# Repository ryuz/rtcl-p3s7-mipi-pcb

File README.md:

English version: [README_en.md](README_en.md)

# グローバルシャッターMIPI高速度カメラ(PYTHON300 + Spartan7)

## 概要

[こちら](https://rtc-lab.com/products/rtcl-cam-p3s7-mipi/)で紹介しておりますグローバルシャッターMIPI高速度カメラの KiCAD による設計データです。

オンセミコンダクター社 [PYTHON300イメージセンサー](https://www.onsemi.jp/products/sensors/image-sensors/python300) と AMD(Xilinx) の [Spartan7](https://www.amd.com/ja/products/adaptive-socs-and-fpgas/fpga/spartan-7.html) FPGA を用いた研究開発向けの小型のカメラモジュールです。

データシート上は VGA サイズながら 815fps の高速度撮影が可能と記載されているセンサーを利用しており、当方では [KV260](https://www.amd.com/ja/products/system-on-modules/kria/k26/kv260-vision-starter-kit.html) と [Zybo Z7](https://digilent.com/shop/zybo-z7-zynq-7000-arm-fpga-soc-development-board/) に接続して 320x320 サイズで 1000fps 撮像が出来ております。

撮影動画なども[こちら](https://rtc-lab.com/products/rtcl-cam-p3s7-mipi/)で紹介しております。

## 回路図

回路図は以下です。

- [イメージセンサー子基板](sensor_python300/sensor_python300.pdf)
- [FPGA親基板](mipi_spartan7/mipi_spartan7.pdf)

## 基板販売

当方で製造したものを[BOOTH](https://rtc-lab.booth.pm/)にて販売中です。

- [モノクロ版](https://rtc-lab.booth.pm/items/7427869)
- [カラー版](https://rtc-lab.booth.pm/items/7428802)

## 関連ソフトウェア

現時点では、KV260 に独自仕様でデータを送るプロジェクトがあります。

- [Spartan-7 のデザイン](https://github.com/ryuz/rtcl-designs/tree/main/projects/rtcl_p3s7_mipi/rtcl_p3s7_mipi)
- [KV260 の デザイン](https://github.com/ryuz/rtcl-designs/tree/main/projects/kv260/kv260_rtcl_p3s7_hs)

他に速度を落として ZYBO と接続できる事や、MIPI-CSI に準拠することも可能なことを確認していますが、まだプロジェクトとして準備できておりませんので今後にご期待ください。

## リポジトリ構成

| ディレクトリ |  説明                                            |
|:------------|:------------------------------------------------|
| mipi_spartan7    | Spartan7 FPGA の載った親基板のプロジェクト |
| sensor_python300 | PYTHON300 イメージセンサーの載った子基板のプロジェクト |
| sensor_mipi      | 親子基板を共取り製造用に結合したプロジェクト |

## 免責事項

本設計データは、研究開発用の試作実験に用するものであり、利用に際して発生した如何なる損害も作者は補償いたしませんので予めご了承ください。

## ライセンス(License)

本設計データは、[クリエイティブ・コモンズ 表示-非営利 4.0 国際 ライセンス](https://creativecommons.org/licenses/by-nc/4.0/deed.ja)の下で提供されています。

製造した本基板の無断での販売や配布を行わない限りは、趣味や研究開発用途でご自由にお使いいただく事が出来ます。

また、商用に製造販売を希望される場合は、別途ライセンス契約を作者までご相談ください。[お問い合わせフォーム](https://rtc-lab.com/contact/)などからお問い合わせ頂けます。

## 作者情報

渕上 竜司(Ryuji Fuchikami)
[リアルタイムコンピューティング研究所](https://rtc-lab.com/)

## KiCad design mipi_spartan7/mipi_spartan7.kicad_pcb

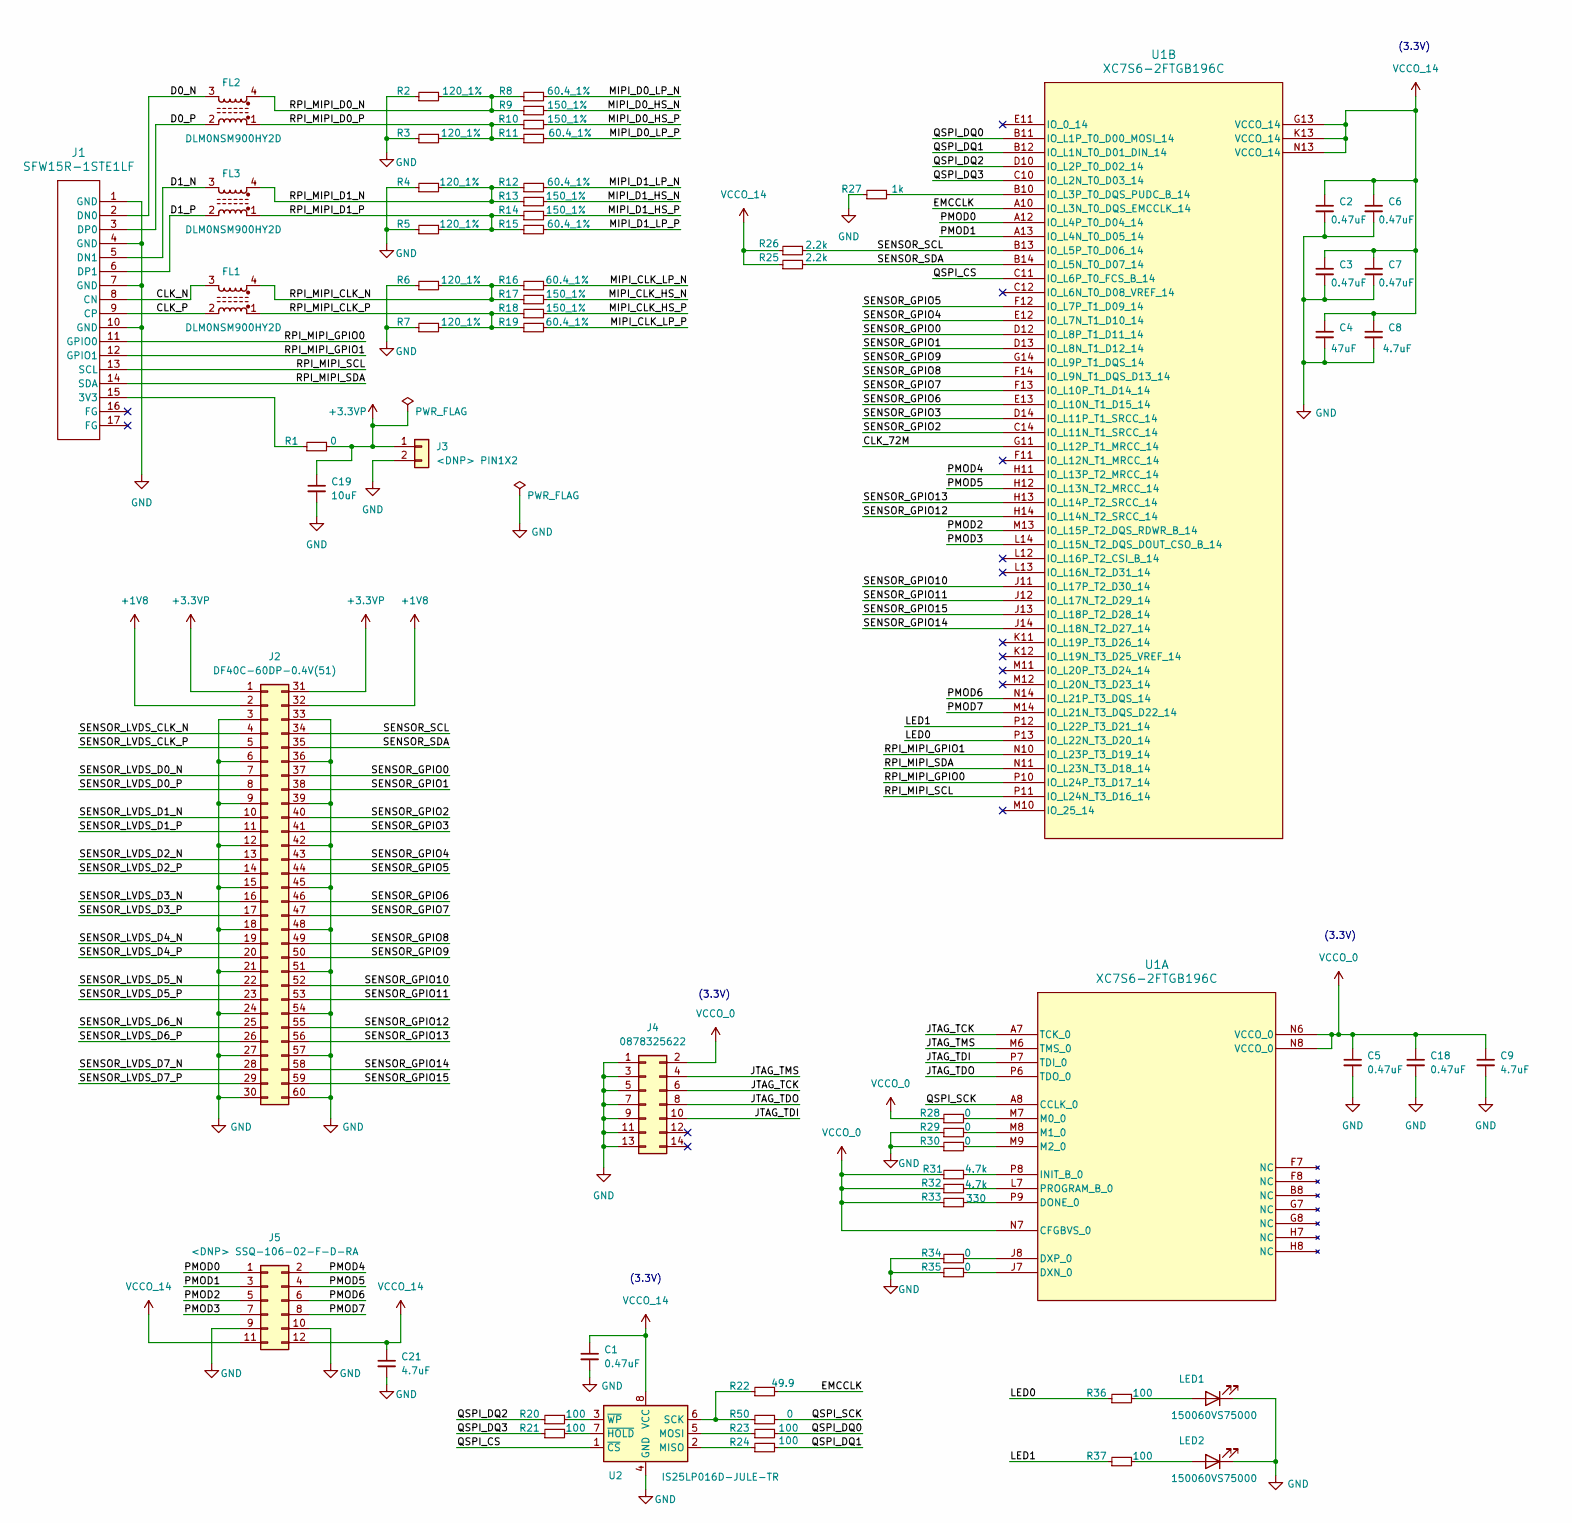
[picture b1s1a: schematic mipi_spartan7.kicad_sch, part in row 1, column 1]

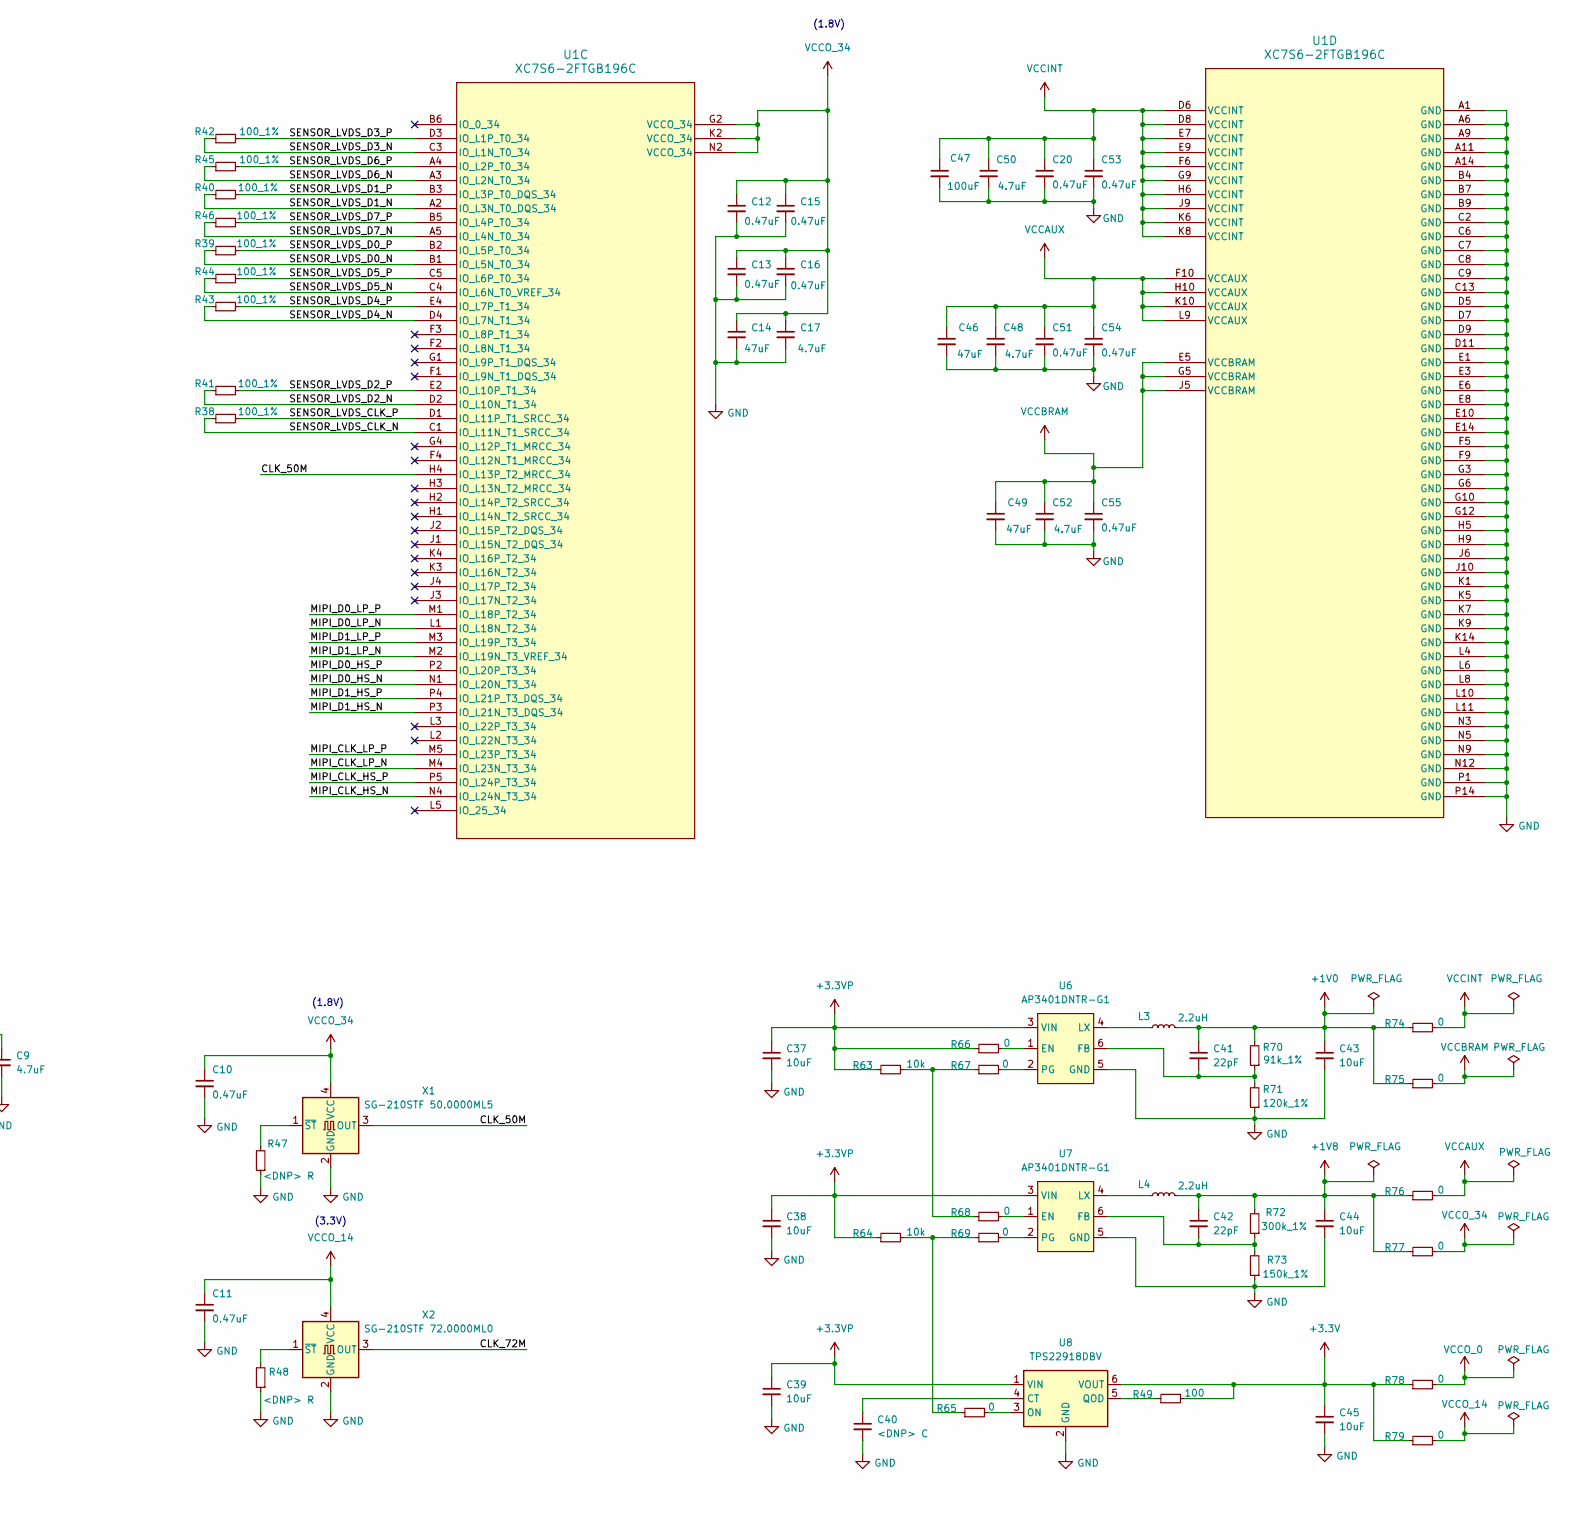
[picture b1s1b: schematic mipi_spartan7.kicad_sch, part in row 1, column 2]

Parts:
C1, C2, C3, C5, C6, C7, C10, C11, C12, C13, C15, C16, C18, C20, C51, C53, C54, C55: 0.47uF; C_0402_1005Metric
C4, C14, C46, C49: 47uF; C_0603_1608Metric
C8, C9, C17, C21, C48, C50, C52: 4.7uF; C_0402_1005Metric
C19, C37, C38, C39, C43, C44, C45: 10uF; C_0603_1608Metric
C40: <DNP> C; L_0402_1005Metric
C41, C42: 22pF; L_0402_1005Metric
C47: 100uF; C_1206_3216Metric
FL1, FL2, FL3: DLM0NSM900HY2D; JLC C1857796
J1: SFW15R-1STE1LF
J2: DF40C-60DP-0.4V(51); DF40C-60DP-0.4V51
J3: <DNP> PIN1X2; PH_01x02_2.54mm_NoSilk
J4: 0878325622; 878325622
J5: <DNP> SSQ-106-02-F-D-RA; PH_02x06_2.54mm
L3, L4: 2.2uH; L_1008_2520Metric
LED1, LED2: 150060VS75000; LED_0603_1608Metric
R1, R28, R29, R30, R34, R35, R50, R65, R66, R67, R68, R69, R74, R75, R76, R77, R78, R79: 0; R_0402_1005Metric
R2, R3, R4, R5, R6, R7: 120_1%; R_0402_1005Metric
R8, R11, R12, R15, R16, R19: 60.4_1%; R_0402_1005Metric
R9, R10, R13, R14, R17, R18: 150_1%; R_0402_1005Metric
R20, R21, R23, R24, R36, R37, R49: 100; R_0402_1005Metric
R22: 49.9; R_0402_1005Metric
R25, R26: 2.2k; R_0402_1005Metric
R27: 1k; R_0402_1005Metric
R31, R32: 4.7k; R_0402_1005Metric
R33: 330; R_0402_1005Metric
R38, R39, R40, R41, R42, R43, R44, R45, R46: 100_1%; R_0402_1005Metric
R47, R48: <DNP> R; R_0402_1005Metric
R63, R64: 10k; R_0402_1005Metric
R70: 91k_1%; R_0402_1005Metric
R71: 120k_1%; R_0402_1005Metric
R72: 300k_1%; R_0402_1005Metric
R73: 150k_1%; R_0402_1005Metric
U1: XC7S6-2FTGB196C; FTGB196
U2: IS25LP016D-JULE-TR
U6, U7: AP3401DNTR-G1; Diodes_UDFN2020-6_Type-J
U8: TPS22918DBV; SOT-23-6
X1: SG-210STF 50.0000ML5; SG-210STF
X2: SG-210STF 72.0000ML0; SG-210STF

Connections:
+1V0: C41.1, C43.1, L3.2, R70.2, R74.1, R75.1
+1V8: C42.1, C44.1, J2.2, J2.32, L4.2, R72.2, R76.1, R77.1
+3.3V: C45.1, R49.2, R78.1, R79.1, U8.6 (VOUT)
+3.3VP: C19.1, C37.1, C38.1, C39.1, J2.1, J2.31, J3.1, R1.2, R63.1, R64.1, R66.1, U6.3 (VIN), U7.3 (VIN), U8.1 (VIN)
/CLK_50M: U1.H4 (IO_L13P_T2_MRCC_34), X1.3 (OUT)
/CLK_72M: U1.G11 (IO_L12P_T1_MRCC_14), X2.3 (OUT)
/CLK_N: FL1.3, J1.8 (CN)
/CLK_P: FL1.2, J1.9 (CP)
/D0_N: FL2.3, J1.2 (DN0)
/D0_P: FL2.2, J1.3 (DP0)
/D1_N: FL3.3, J1.5 (DN1)
/D1_P: FL3.2, J1.6 (DP1)
/EMCCLK: R22.2, U1.A10 (IO_L3N_T0_DQS_EMCCLK_14)
/JTAG_TCK: J4.6, U1.A7 (TCK_0)
/JTAG_TDI: J4.10, U1.P7 (TDI_0)
/JTAG_TDO: J4.8, U1.P6 (TDO_0)
/JTAG_TMS: J4.4, U1.M6 (TMS_0)
/LED0: R36.1, U1.P13 (IO_L22N_T3_D20_14)
/LED1: R37.1, U1.P12 (IO_L22P_T3_D21_14)
/MIPI_CLK_HS_N: R17.2, U1.N4 (IO_L24N_T3_34)
/MIPI_CLK_HS_P: R18.2, U1.P5 (IO_L24P_T3_34)
/MIPI_CLK_LP_N: R16.2, U1.M4 (IO_L23N_T3_34)
/MIPI_CLK_LP_P: R19.2, U1.M5 (IO_L23P_T3_34)
/MIPI_D0_HS_N: R9.2, U1.N1 (IO_L20N_T3_34)
/MIPI_D0_HS_P: R10.2, U1.P2 (IO_L20P_T3_34)
/MIPI_D0_LP_N: R8.2, U1.L1 (IO_L18N_T2_34)
/MIPI_D0_LP_P: R11.2, U1.M1 (IO_L18P_T2_34)
/MIPI_D1_HS_N: R13.2, U1.P3 (IO_L21N_T3_DQS_34)
/MIPI_D1_HS_P: R14.2, U1.P4 (IO_L21P_T3_DQS_34)
/MIPI_D1_LP_N: R12.2, U1.M2 (IO_L19N_T3_VREF_34)
/MIPI_D1_LP_P: R15.2, U1.M3 (IO_L19P_T3_34)
/PMOD0: J5.1, U1.A12 (IO_L4P_T0_D04_14)
/PMOD1: J5.3, U1.A13 (IO_L4N_T0_D05_14)
/PMOD2: J5.5, U1.M13 (IO_L15P_T2_DQS_RDWR_B_14)
/PMOD3: J5.7, U1.L14 (IO_L15N_T2_DQS_DOUT_CSO_B_14)
/PMOD4: J5.2, U1.H11 (IO_L13P_T2_MRCC_14)
/PMOD5: J5.4, U1.H12 (IO_L13N_T2_MRCC_14)
/PMOD6: J5.6, U1.N14 (IO_L21P_T3_DQS_14)
/PMOD7: J5.8, U1.M14 (IO_L21N_T3_DQS_D22_14)
/QSPI_CS: U1.C11 (IO_L6P_T0_FCS_B_14), U2.1 (~CS)
/QSPI_DQ0: R23.2, U1.B11 (IO_L1P_T0_D00_MOSI_14)
/QSPI_DQ1: R24.2, U1.B12 (IO_L1N_T0_D01_DIN_14)
/QSPI_DQ2: R20.1, U1.D10 (IO_L2P_T0_D02_14)
/QSPI_DQ3: R21.1, U1.C10 (IO_L2N_T0_D03_14)
/QSPI_SCK: R50.2, U1.A8 (CCLK_0)
/RPI_MIPI_CLK_N: FL1.4, R6.2, R16.1, R17.1
/RPI_MIPI_CLK_P: FL1.1, R7.2, R18.1, R19.1
/RPI_MIPI_D0_N: FL2.4, R2.2, R8.1, R9.1
/RPI_MIPI_D0_P: FL2.1, R3.2, R10.1, R11.1
/RPI_MIPI_D1_N: FL3.4, R4.2, R12.1, R13.1
/RPI_MIPI_D1_P: FL3.1, R5.2, R14.1, R15.1
/RPI_MIPI_GPIO0: J1.11 (GPIO0), U1.P10 (IO_L24P_T3_D17_14)
/RPI_MIPI_GPIO1: J1.12 (GPIO1), U1.N10 (IO_L23P_T3_D19_14)
/RPI_MIPI_SCL: J1.13 (SCL), U1.P11 (IO_L24N_T3_D16_14)
/RPI_MIPI_SDA: J1.14 (SDA), U1.N11 (IO_L23N_T3_D18_14)
/SENSOR_GPIO0: J2.37, U1.D12 (IO_L8P_T1_D11_14)
/SENSOR_GPIO1: J2.38, U1.D13 (IO_L8N_T1_D12_14)
/SENSOR_GPIO2: J2.40, U1.C14 (IO_L11N_T1_SRCC_14)
/SENSOR_GPIO3: J2.41, U1.D14 (IO_L11P_T1_SRCC_14)
/SENSOR_GPIO4: J2.43, U1.E12 (IO_L7N_T1_D10_14)
/SENSOR_GPIO5: J2.44, U1.F12 (IO_L7P_T1_D09_14)
/SENSOR_GPIO6: J2.46, U1.E13 (IO_L10N_T1_D15_14)
/SENSOR_GPIO7: J2.47, U1.F13 (IO_L10P_T1_D14_14)
/SENSOR_GPIO8: J2.49, U1.F14 (IO_L9N_T1_DQS_D13_14)
/SENSOR_GPIO9: J2.50, U1.G14 (IO_L9P_T1_DQS_14)
/SENSOR_GPIO10: J2.52, U1.J11 (IO_L17P_T2_D30_14)
/SENSOR_GPIO11: J2.53, U1.J12 (IO_L17N_T2_D29_14)
/SENSOR_GPIO12: J2.55, U1.H14 (IO_L14N_T2_SRCC_14)
/SENSOR_GPIO13: J2.56, U1.H13 (IO_L14P_T2_SRCC_14)
/SENSOR_GPIO14: J2.58, U1.J14 (IO_L18N_T2_D27_14)
/SENSOR_GPIO15: J2.59, U1.J13 (IO_L18P_T2_D28_14)
/SENSOR_LVDS_CLK_N: J2.4, R38.1, U1.C1 (IO_L11N_T1_SRCC_34)
/SENSOR_LVDS_CLK_P: J2.5, R38.2, U1.D1 (IO_L11P_T1_SRCC_34)
/SENSOR_LVDS_D0_N: J2.7, R39.1, U1.B1 (IO_L5N_T0_34)
/SENSOR_LVDS_D0_P: J2.8, R39.2, U1.B2 (IO_L5P_T0_34)
/SENSOR_LVDS_D1_N: J2.10, R40.1, U1.A2 (IO_L3N_T0_DQS_34)
/SENSOR_LVDS_D1_P: J2.11, R40.2, U1.B3 (IO_L3P_T0_DQS_34)
/SENSOR_LVDS_D2_N: J2.13, R41.1, U1.D2 (IO_L10N_T1_34)
/SENSOR_LVDS_D2_P: J2.14, R41.2, U1.E2 (IO_L10P_T1_34)
/SENSOR_LVDS_D3_N: J2.16, R42.1, U1.C3 (IO_L1N_T0_34)
/SENSOR_LVDS_D3_P: J2.17, R42.2, U1.D3 (IO_L1P_T0_34)
/SENSOR_LVDS_D4_N: J2.19, R43.1, U1.D4 (IO_L7N_T1_34)
/SENSOR_LVDS_D4_P: J2.20, R43.2, U1.E4 (IO_L7P_T1_34)
/SENSOR_LVDS_D5_N: J2.22, R44.1, U1.C4 (IO_L6N_T0_VREF_34)
/SENSOR_LVDS_D5_P: J2.23, R44.2, U1.C5 (IO_L6P_T0_34)
/SENSOR_LVDS_D6_N: J2.25, R45.1, U1.A3 (IO_L2N_T0_34)
/SENSOR_LVDS_D6_P: J2.26, R45.2, U1.A4 (IO_L2P_T0_34)
/SENSOR_LVDS_D7_N: J2.28, R46.1, U1.A5 (IO_L4N_T0_34)
/SENSOR_LVDS_D7_P: J2.29, R46.2, U1.B5 (IO_L4P_T0_34)
/SENSOR_SCL: J2.34, R26.2, U1.B13 (IO_L5P_T0_D06_14)
/SENSOR_SDA: J2.35, R25.2, U1.B14 (IO_L5N_T0_D07_14)
GND: C1.2, C2.2, C3.2, C4.2, C5.2, C6.2, C7.2, C8.2, C9.2, C10.2, C11.2, C12.2, C13.2, C14.2, C15.2, C16.2, C17.2, C18.2, C19.2, C20.2, C21.2, C37.2, C38.2, C39.2, C40.2, C43.2, C44.2, C45.2, C46.2, C47.2, C48.2, C49.2, C50.2, C51.2, C52.2, C53.2, C54.2, C55.2, J1.1 (GND), J1.4 (GND), J1.7 (GND), J1.10 (GND), J2.3, J2.6, J2.9, J2.12, J2.15, J2.18, J2.21, J2.24, J2.27, J2.30, J2.33, J2.36, J2.39, J2.42, J2.45, J2.48, J2.51, J2.54, J2.57, J2.60, J3.2, J4.1, J4.3, J4.5, J4.7, J4.9, J4.11, J4.13, J5.9, J5.10, LED1.1 (K), LED2.1 (K), R2.1, R3.1, R4.1, R5.1, R6.1, R7.1, R27.1, R29.1, R30.1, R34.1, R35.1, R47.1, R48.1, R71.1, R73.1, U1.A1 (GND), U1.A6 (GND), U1.A9 (GND), U1.A11 (GND), U1.A14 (GND), U1.B4 (GND), U1.B7 (GND), U1.B9 (GND), U1.C2 (GND), U1.C6 (GND), U1.C7 (GND), U1.C8 (GND), U1.C9 (GND), U1.C13 (GND), U1.D5 (GND), U1.D7 (GND), U1.D9 (GND), U1.D11 (GND), U1.E1 (GND), U1.E3 (GND), U1.E6 (GND), U1.E8 (GND), U1.E10 (GND), U1.E14 (GND), U1.F5 (GND), U1.F9 (GND), U1.G3 (GND), U1.G6 (GND), U1.G10 (GND), U1.G12 (GND), U1.H5 (GND), U1.H9 (GND), U1.J6 (GND), U1.J10 (GND), U1.K1 (GND), U1.K5 (GND), U1.K7 (GND), U1.K9 (GND), U1.K14 (GND), U1.L4 (GND), U1.L6 (GND), U1.L8 (GND), U1.L10 (GND), U1.L11 (GND), U1.N3 (GND), U1.N5 (GND), U1.N9 (GND), U1.N12 (GND), U1.P1 (GND), U1.P14 (GND), U2.4 (GND), U6.5 (GND), U7.5 (GND), U8.2 (GND), X1.2 (GND), X2.2 (GND)
unnamed: J1.15 (3V3), R1.1
unnamed: LED1.2 (A), R36.2
unnamed: LED2.2 (A), R37.2
unnamed: R63.2, R67.1, R68.1
unnamed: R64.2, R65.1, R69.1
unnamed: R33.2, U1.P9 (DONE_0)
unnamed: R35.2, U1.J7 (DXN_0)
unnamed: R34.2, U1.J8 (DXP_0)
unnamed: R31.2, U1.P8 (INIT_B_0)
unnamed: R28.2, U1.M7 (M0_0)
unnamed: R29.2, U1.M8 (M1_0)
unnamed: R30.2, U1.M9 (M2_0)
unnamed: R32.2, U1.L7 (PROGRAM_B_0)
unnamed: R27.2, U1.B10 (IO_L3P_T0_DQS_PUDC_B_14)
unnamed: R24.1, U2.2 (MISO)
unnamed: R23.1, U2.5 (MOSI)
unnamed: R22.1, R50.1, U2.6 (SCK)
unnamed: R21.2, U2.7 (~HOLD)
unnamed: R20.2, U2.3 (~WP)
unnamed: R66.2, U6.1 (EN)
unnamed: C41.2, R70.1, R71.2, U6.6 (FB)
unnamed: L3.1, U6.4 (LX)
unnamed: R67.2, U6.2 (PG)
unnamed: R68.2, U7.1 (EN)
unnamed: C42.2, R72.1, R73.2, U7.6 (FB)
unnamed: L4.1, U7.4 (LX)
unnamed: R69.2, U7.2 (PG)
unnamed: C40.1, U8.4 (CT)
unnamed: R65.2, U8.3 (ON)
unnamed: R49.1, U8.5 (QOD)
unnamed: R47.2, X1.1 (~ST)
unnamed: R48.2, X2.1 (~ST)
VCCAUX: C46.1, C48.1, C51.1, C54.1, R76.2, U1.F10 (VCCAUX), U1.H10 (VCCAUX), U1.K10 (VCCAUX), U1.L9 (VCCAUX)
VCCBRAM: C49.1, C52.1, C55.1, R75.2, U1.E5 (VCCBRAM), U1.G5 (VCCBRAM), U1.J5 (VCCBRAM)
VCCINT: C20.1, C47.1, C50.1, C53.1, R74.2, U1.D6 (VCCINT), U1.D8 (VCCINT), U1.E7 (VCCINT), U1.E9 (VCCINT), U1.F6 (VCCINT), U1.G9 (VCCINT), U1.H6 (VCCINT), U1.J9 (VCCINT), U1.K6 (VCCINT), U1.K8 (VCCINT)
VCCO_0: C5.1, C9.1, C18.1, J4.2, R28.1, R31.1, R32.1, R33.1, R78.2, U1.N6 (VCCO_0), U1.N7 (CFGBVS_0), U1.N8 (VCCO_0)
VCCO_14: C1.1, C2.1, C3.1, C4.1, C6.1, C7.1, C8.1, C11.1, C21.1, J5.11, J5.12, R25.1, R26.1, R79.2, U1.G13 (VCCO_14), U1.K13 (VCCO_14), U1.N13 (VCCO_14), U2.8 (VCC), X2.4 (VCC)
VCCO_34: C10.1, C12.1, C13.1, C14.1, C15.1, C16.1, C17.1, R77.2, U1.G2 (VCCO_34), U1.K2 (VCCO_34), U1.N2 (VCCO_34), X1.4 (VCC)

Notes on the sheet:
(1.8V)
(3.3V)

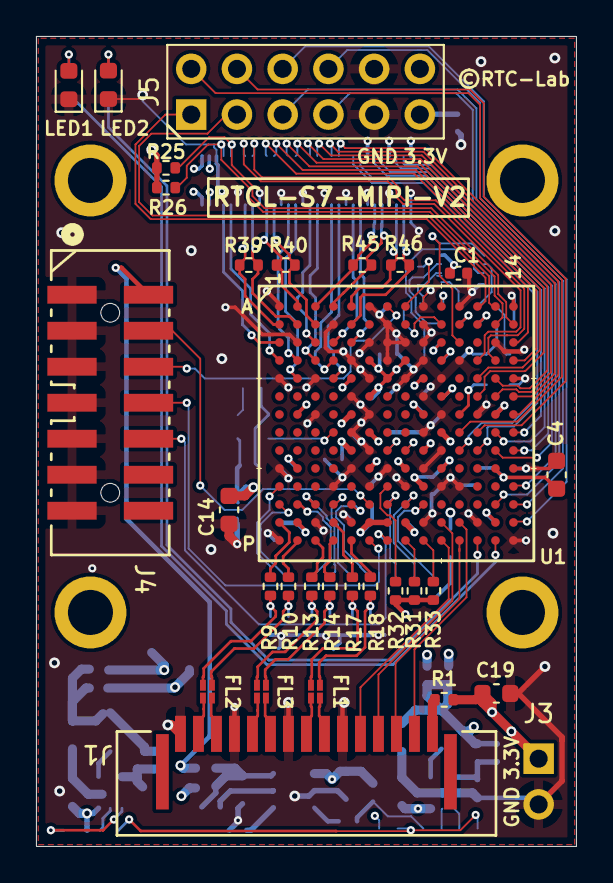
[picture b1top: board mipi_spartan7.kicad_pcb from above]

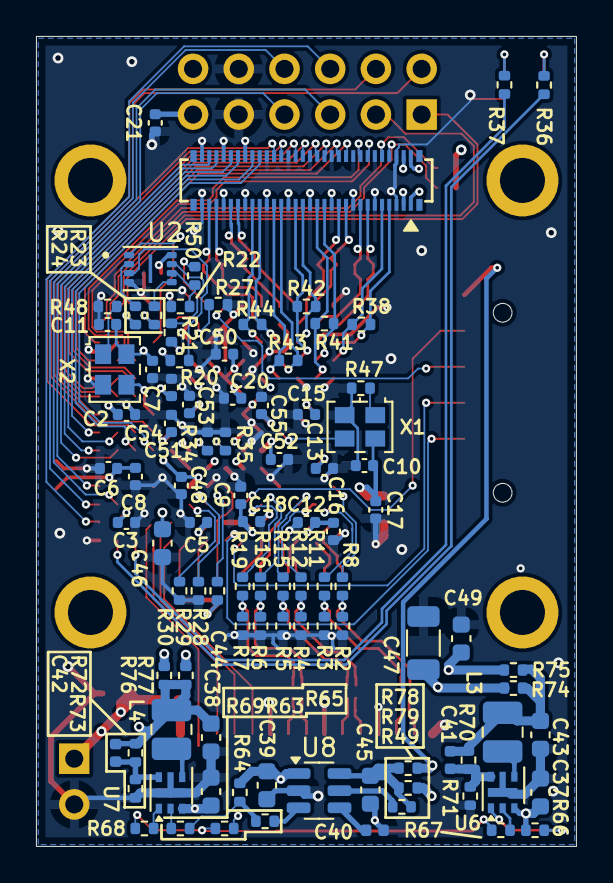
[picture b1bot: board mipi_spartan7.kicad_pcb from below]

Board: 4 copper layers, 30.0 x 45.0 mm, 126 parts (96 on the bottom side), 130 nets.

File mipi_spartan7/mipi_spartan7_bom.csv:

"Reference","Value","Datasheet","Footprint","Qty","DNP"
"C1,C2,C3,C5,C6,C7,C10,C11,C12,C13,C15,C16,C18,C20,C51,C53,C54,C55","0.47uF","~","Capacitor_SMD:C_0402_1005Metric","18",""
"C4,C14,C46,C49","47uF","~","Capacitor_SMD:C_0603_1608Metric","4",""
"C8,C9,C17,C21,C48,C50,C52","4.7uF","~","Capacitor_SMD:C_0402_1005Metric","7",""
"C19,C37,C38,C39,C43,C44,C45","10uF","~","Capacitor_SMD:C_0603_1608Metric","7",""
"C40","<DNP> C","~","Inductor_SMD:L_0402_1005Metric","1",""
"C41,C42","22pF","~","Inductor_SMD:L_0402_1005Metric","2",""
"C47","100uF","~","Capacitor_SMD:C_1206_3216Metric","1",""
"FL1,FL2,FL3","DLM0NSM900HY2D","~","mipi_spartan7:DLM0NSM900HY2D","3",""
"J1","SFW15R-1STE1LF","SFW15R-1STE1LF","mipi_spartan7:SFW15R-1STE1LF","1",""
"J2","DF40C-60DP-0.4V(51)","~","mipi_spartan7:DF40C-60DP-0.4V51","1",""
"J3","<DNP> PIN1X2","~","mipi_spartan7:PH_01x02_2.54mm_NoSilk","1",""
"J4","0878325622","~","mipi_spartan7:878325622","1",""
"J5","<DNP> SSQ-106-02-F-D-RA","~","mipi_spartan7:PH_02x06_2.54mm","1",""
"L3,L4","2.2uH","~","Inductor_SMD:L_1008_2520Metric","2",""
"LED1,LED2","150060VS75000","~","LED_SMD:LED_0603_1608Metric","2",""
"R1,R28,R29,R30,R34,R35,R50,R65,R66,R67,R68,R69,R74,R75,R76,R77,R78,R79","0","~","Resistor_SMD:R_0402_1005Metric","18",""
"R2,R3,R4,R5,R6,R7","120_1%","~","Resistor_SMD:R_0402_1005Metric","6",""
"R8,R11,R12,R15,R16,R19","60.4_1%","~","Resistor_SMD:R_0402_1005Metric","6",""
"R9,R10,R13,R14,R17,R18","150_1%","~","Resistor_SMD:R_0402_1005Metric","6",""
"R20,R21,R23,R24,R36,R37,R49","100","~","Resistor_SMD:R_0402_1005Metric","7",""
"R22","49.9","~","Resistor_SMD:R_0402_1005Metric","1",""
"R25,R26","2.2k","~","Resistor_SMD:R_0402_1005Metric","2",""
"R27","1k","~","Resistor_SMD:R_0402_1005Metric","1",""
"R31,R32","4.7k","~","Resistor_SMD:R_0402_1005Metric","2",""
"R33","330","~","Resistor_SMD:R_0402_1005Metric","1",""
"R38,R39,R40,R41,R42,R43,R44,R45,R46","100_1%","~","Resistor_SMD:R_0402_1005Metric","9",""
"R47,R48","<DNP> R","~","Resistor_SMD:R_0402_1005Metric","2",""
"R63,R64","10k","~","Resistor_SMD:R_0402_1005Metric","2",""
"R70","91k_1%","~","Resistor_SMD:R_0402_1005Metric","1",""
"R71","120k_1%","~","Resistor_SMD:R_0402_1005Metric","1",""
"R72","300k_1%","~","Resistor_SMD:R_0402_1005Metric","1",""
"R73","150k_1%","~","Resistor_SMD:R_0402_1005Metric","1",""
"U1","XC7S6-2FTGB196C","XC7S6-1FTGB196C","mipi_spartan7:FTGB196","1",""
"U2","IS25LP016D-JULE-TR","http://ww1.microchip.com/downloads/en/DeviceDoc/Atmel-8707-S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","mipi_spartan7:IS25LP016D-JULE-TR","1",""
"U6,U7","AP3401DNTR-G1","","mipi_spartan7:Diodes_UDFN2020-6_Type-J","2",""
"U8","TPS22918DBV","http://www.ti.com/lit/ds/symlink/tps22917.pdf","Package_TO_SOT_SMD:SOT-23-6","1",""
"X1","SG-210STF 50.0000ML5","https://support.epson.biz/td/api/doc_check.php?dl=brief_SG50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","Oscillator:Oscillator_SMD_SeikoEpson_SG8002LB-4Pin_5.0x3.2mm","1",""
"X2","SG-210STF 72.0000ML0","https://support.epson.biz/td/api/doc_check.php?dl=brief_SG50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","Oscillator:Oscillator_SMD_SeikoEpson_SG8002LB-4Pin_5.0x3.2mm","1",""

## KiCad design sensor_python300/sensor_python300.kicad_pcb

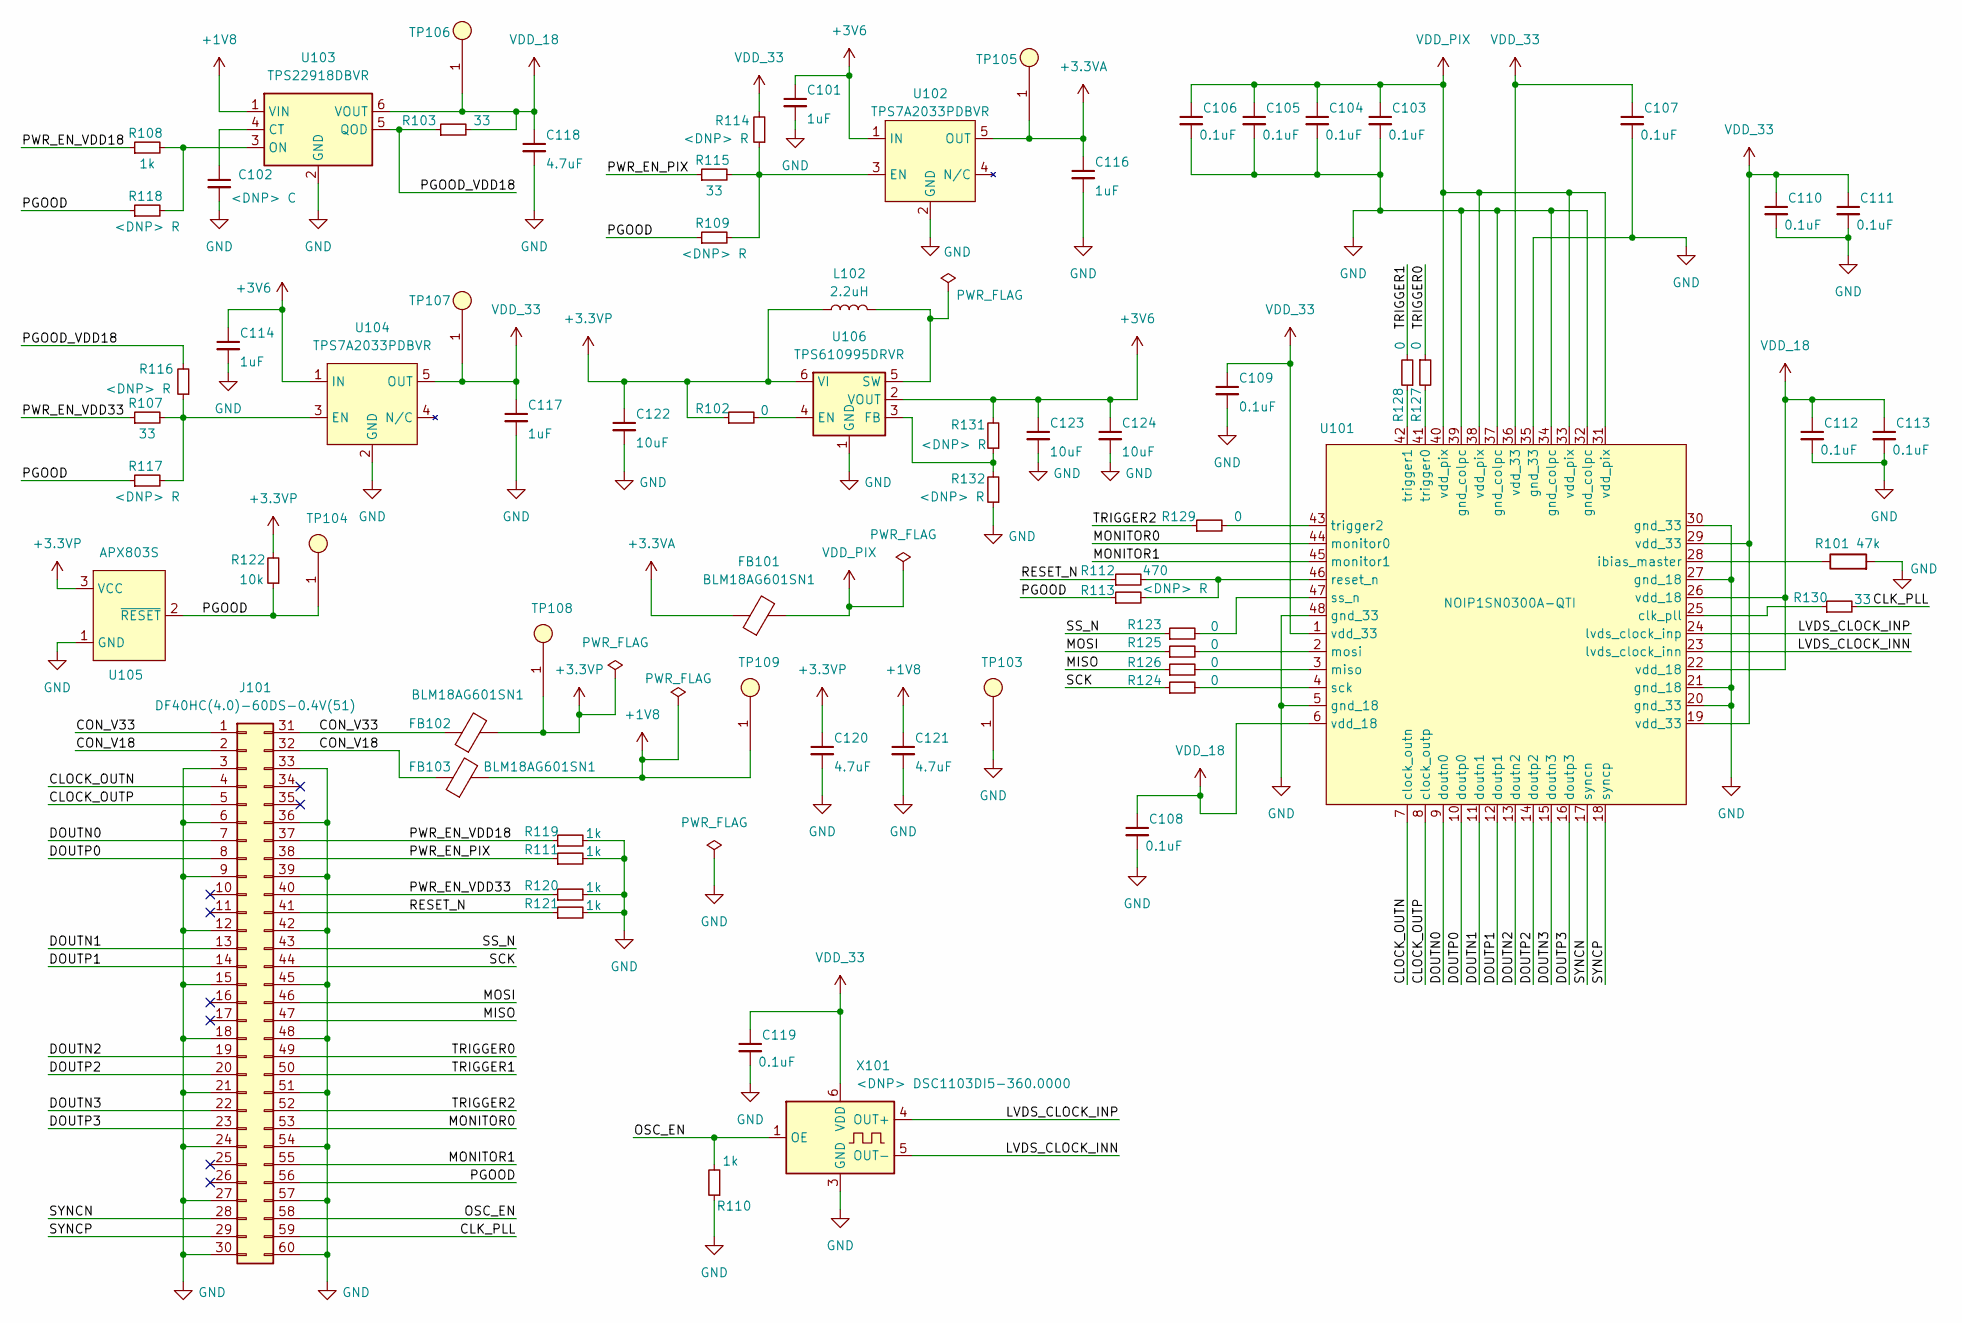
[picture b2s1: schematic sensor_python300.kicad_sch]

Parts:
C101, C114, C116, C117: 1uF; C_0402_1005Metric
C102: <DNP> C; C_0402_1005Metric
C103, C104, C105, C106, C107, C108, C109, C110, C111, C112, C113, C119: 0.1uF; C_0402_1005Metric
C118, C120, C121: 4.7uF; C_0402_1005Metric
C122, C123, C124: 10uF; C_0603_1608Metric
FB101, FB102, FB103: BLM18AG601SN1; L_0603_1608Metric
J101: DF40HC(4.0)-60DS-0.4V(51); DF40HC4.0-60DS-0.4V51
L102: 2.2uH; L_1008_2520Metric
R101: 47k; R_0402_1005Metric
R102, R123, R124, R125, R126, R127, R128, R129: 0; R_0402_1005Metric
R103, R107, R115, R130: 33; R_0402_1005Metric
R108, R110, R111, R119, R120, R121: 1k; R_0402_1005Metric
R109, R113, R114, R116, R117, R118, R131, R132: <DNP> R; R_0402_1005Metric
R112: 470; R_0402_1005Metric
R122: 10k; R_0402_1005Metric
TP103, TP104, TP105, TP106, TP107, TP108, TP109: TestPin
U101: NOIP1SN0300A-QTI; NOIP1SN1300A
U102, U104: TPS7A2033PDBVR; SOT-23-5
U103: TPS22918DBVR; SOT-23-6
U105: APX803S; SOT-23-3
U106: TPS610995DRVR; WSON-6-1EP_2x2mm_P0.65mm_EP1x1.6mm
X101: <DNP> DSC1103DI5-360.0000; Oscillator_SMD_SiTime_PQFD-6L_3.2x2.5mm

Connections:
+1V8: C121.1, FB103.2, TP109.1, U103.1 (VIN)
+3.3VA: C116.1, FB101.1, TP105.1, U102.5 (OUT)
+3.3VP: C120.1, C122.1, FB102.2, L102.1, R102.1, R122.2, TP108.1, U105.3 (VCC), U106.6 (VI)
+3V6: C101.1, C114.1, C123.1, C124.1, R131.2, U102.1 (IN), U104.1 (IN), U106.2 (VOUT)
/CLK_PLL: J101.59, R130.2
/CLOCK_OUTN: J101.4, U101.7 (clock_outn)
/CLOCK_OUTP: J101.5, U101.8 (clock_outp)
/CON_V18: FB103.1, J101.2, J101.32
/CON_V33: FB102.1, J101.1, J101.31
/DOUTN0: J101.7, U101.9 (doutn0)
/DOUTN1: J101.13, U101.11 (doutn1)
/DOUTN2: J101.19, U101.13 (doutn2)
/DOUTN3: J101.22, U101.15 (doutn3)
/DOUTP0: J101.8, U101.10 (doutp0)
/DOUTP1: J101.14, U101.12 (doutp1)
/DOUTP2: J101.20, U101.14 (doutp2)
/DOUTP3: J101.23, U101.16 (doutp3)
/LVDS_CLOCK_INN: U101.23 (lvds_clock_inn), X101.5 (OUT-)
/LVDS_CLOCK_INP: U101.24 (lvds_clock_inp), X101.4 (OUT+)
/MISO: J101.47, R126.1
/MONITOR0: J101.53, U101.44 (monitor0)
/MONITOR1: J101.55, U101.45 (monitor1)
/MOSI: J101.46, R125.1
/OSC_EN: J101.58, R110.2, X101.1 (OE)
/PGOOD: J101.56, R109.1, R113.1, R117.1, R118.1, R122.1, TP104.1, U105.2 (~RESET)
/PGOOD_VDD18: R103.1, R116.2, U103.5 (QOD)
/PWR_EN_PIX: J101.38, R111.1, R115.1
/PWR_EN_VDD18: J101.37, R108.1, R119.1
/PWR_EN_VDD33: J101.40, R107.1, R120.1
/RESET_N: J101.41, R112.1, R121.1
/SCK: J101.44, R124.1
/SS_N: J101.43, R123.1
/SYNCN: J101.28, U101.17 (syncn)
/SYNCP: J101.29, U101.18 (syncp)
/TRIGGER0: J101.49, R127.1
/TRIGGER1: J101.50, R128.2
/TRIGGER2: J101.52, R129.1
GND: C101.2, C102.2, C103.2, C104.2, C105.2, C106.2, C107.2, C108.2, C109.2, C110.2, C111.2, C112.2, C113.2, C114.2, C116.2, C117.2, C118.2, C119.2, C120.2, C121.2, C122.2, C123.2, C124.2, J101.3, J101.6, J101.9, J101.12, J101.15, J101.18, J101.21, J101.24, J101.27, J101.30, J101.33, J101.36, J101.39, J101.42, J101.45, J101.48, J101.51, J101.54, J101.57, J101.60, R101.2, R110.1, R111.2, R119.2, R120.2, R121.2, R132.1, TP103.1, U101.5 (gnd_18), U101.20 (gnd_33), U101.21 (gnd_18), U101.27 (gnd_18), U101.30 (gnd_33), U101.32 (gnd_colpc), U101.34 (gnd_colpc), U101.35 (gnd_33), U101.37 (gnd_colpc), U101.39 (gnd_colpc), U101.48 (gnd_33), U102.2 (GND), U103.2 (GND), U104.2 (GND), U105.1 (GND), U106.1 (GND), U106.7 (GND), X101.3 (GND)
unnamed: R130.1, U101.25 (clk_pll)
unnamed: R101.1, U101.28 (ibias_master)
unnamed: R126.2, U101.3 (miso)
unnamed: R125.2, U101.2 (mosi)
unnamed: R112.2, R113.2, U101.46 (reset_n)
unnamed: R124.2, U101.4 (sck)
unnamed: R123.2, U101.47 (ss_n)
unnamed: R127.2, U101.41 (trigger0)
unnamed: R128.1, U101.42 (trigger1)
unnamed: R129.2, U101.43 (trigger2)
unnamed: R109.2, R114.1, R115.2, U102.3 (EN)
unnamed: C102.1, U103.4 (CT)
unnamed: R108.2, R118.2, U103.3 (ON)
unnamed: R107.2, R116.1, R117.2, U104.3 (EN)
unnamed: R102.2, U106.4 (EN)
unnamed: R131.1, R132.2, U106.3 (FB)
unnamed: L102.2, U106.5 (SW)
VDD_18: C108.1, C112.1, C113.1, C118.1, R103.2, TP106.1, U101.6 (vdd_18), U101.22 (vdd_18), U101.26 (vdd_18), U103.6 (VOUT)
VDD_33: C107.1, C109.1, C110.1, C111.1, C117.1, C119.1, R114.2, TP107.1, U101.1 (vdd_33), U101.19 (vdd_33), U101.29 (vdd_33), U101.36 (vdd_33), U104.5 (OUT), X101.6 (VDD)
VDD_PIX: C103.1, C104.1, C105.1, C106.1, FB101.2, U101.31 (vdd_pix), U101.33 (vdd_pix), U101.38 (vdd_pix), U101.40 (vdd_pix)

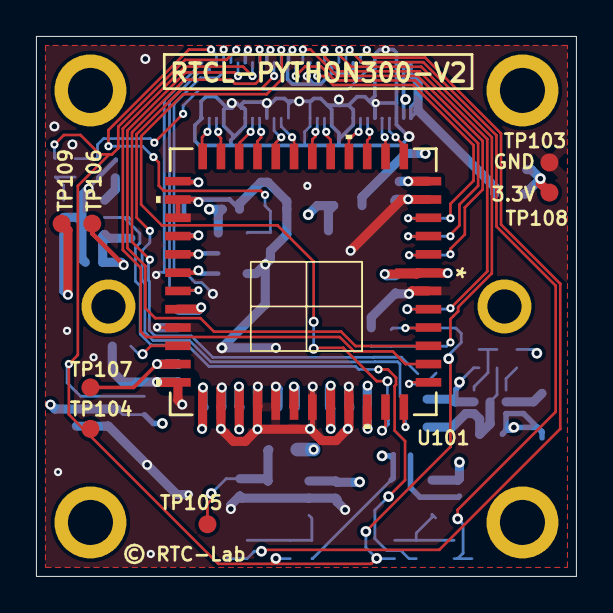
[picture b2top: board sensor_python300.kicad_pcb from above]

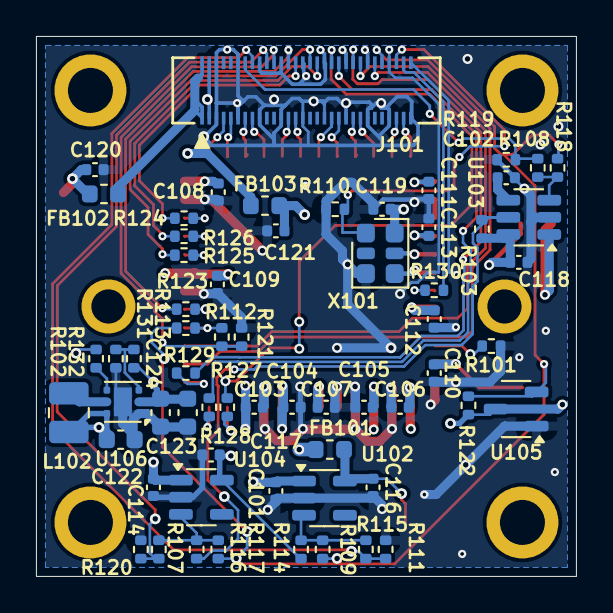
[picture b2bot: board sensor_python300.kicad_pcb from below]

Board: 4 copper layers, 30.0 x 30.0 mm, 71 parts (63 on the bottom side), 58 nets.

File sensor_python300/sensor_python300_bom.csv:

Reference,Value,Datasheet,Footprint,Qty,DNP
"C101,C114,C116,C117",1uF,~,Capacitor_SMD:C_0402_1005Metric,4,
C102,<DNP> C,~,Capacitor_SMD:C_0402_1005Metric,1,
"C103,C104,C105,C106,C107,C108,C109,C110,C111,C112,C113,C119",0.1uF,~,Capacitor_SMD:C_0402_1005Metric,12,
"C118,C120,C121",4.7uF,~,Capacitor_SMD:C_0402_1005Metric,3,
"C122,C123,C124",10uF,~,Capacitor_SMD:C_0402_1005Metric,3,
"FB101,FB102,FB103",BLM18AG601SN1,~,Inductor_SMD:L_0603_1608Metric,3,
J101,DF40HC(4.0)-60DS-0.4V(51),~,sensor_python300:DF40HC4.0-60DS-0.4V51,1,
L102,2.2uH,~,Inductor_SMD:L_1008_2520Metric,1,
R101,47k,~,Resistor_SMD:R_0402_1005Metric,1,
"R102,R123,R124,R125,R126,R127,R128,R129",0,~,Resistor_SMD:R_0402_1005Metric,8,
"R103,R107,R115,R130",33,~,Resistor_SMD:R_0402_1005Metric,4,
"R108,R110,R111,R119,R120,R121",1k,~,Resistor_SMD:R_0402_1005Metric,6,
"R109,R113,R114,R116,R117,R118,R131,R132",<DNP> R,~,Resistor_SMD:R_0402_1005Metric,8,
R112,470,~,Resistor_SMD:R_0402_1005Metric,1,
R122,10k,~,Resistor_SMD:R_0402_1005Metric,1,
"TP103,TP104,TP105,TP106,TP107,TP108,TP109",~,,sensor_python300:TestPin,7,
U101,NOIP1SN0300A-QTI,,sensor_python300:NOIP1SN1300A,1,
"U102,U104",TPS7A2033PDBVR,,Package_TO_SOT_SMD:SOT-23-5,2,
U103,TPS22918DBVR,http://www.ti.com/lit/ds/symlink/tps22917.pdf,Package_TO_SOT_SMD:SOT-23-6,1,
U105,APX803S,,Package_TO_SOT_SMD:SOT-23-3,1,
U106,TPS610995DRVR,https://www.ti.com/lit/gpn/TPS61099,Package_SON:WSON-6-1EP_2x2mm_P0.65mm_EP1x1.6mm,1,
X101,<DNP> DSC1103DI5-360.0000,https://www.sitime.com/datasheet/SiT9366,Oscillator:Oscillator_SMD_SiTime_PQFD-6L_3.2x2.5mm,1,

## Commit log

2025-08-03 1st commit
2025-09-15 電源回路を昇圧DC-DCを使うものに変更
2025-09-15 生成した設計データを追加
2025-09-15 Add English README and improve KiCad project error handling
2025-09-15 Add sections for board sales and related software in README
2025-09-15 Improve clarity in README by specifying the products available for sale on BOOTH
2025-09-15 Add detailed sections for board sales and related software in README
2025-09-15 Refine overview sections in README and README_en for clarity and consistency
2025-09-23 Enhance README and README_en by adding details about the Zybo Z7 connection and including a link to sample videos for better clarity and information.
2025-09-27 Update links for Spartan-7 design in README and README_en to reflect the correct project path
2025-09-30 update URL
2025-09-30 Fix links to Spartan-7 design in README and README_en for accurate project path
2025-10-28 add rule

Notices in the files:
mipi_spartan7/mipi_spartan7.kicad_pcb:
©RTC-Lab
